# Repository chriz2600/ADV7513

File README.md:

# ADV7513

This is a small development board for the [Analog Devices ADV7513 HDMI Transmitter][ADV7513]. It's designed to be hand-soldered.
I also wrote some code for initialisation (via I2C) in verilog. This can be found as part of my [Dreamcast HDMI][DreamcastHDMI] project. 

[![board][oshpark]][oshparkorder]

[ADV7513]: http://www.analog.com/en/products/audio-video/analoghdmidvi-interfaces/analog-hdmidvi-display-interfaces/adv7513.html
[DreamcastHDMI]: https://github.com/chriz2600/DreamcastHDMI/tree/master/FPGA-CycloneIV-ADV7513

[oshparkorder]: https://oshpark.com/shared_projects/b1enkRm7
[oshpark]: https://oshpark.com/assets/badge-5b7ec47045b78aef6eb9d83b3bac6b1920de805e9a0c227658eac6e19a045b9c.png

### BOM

- `U1`: [ADV7513](http://www.analog.com/en/products/audio-video/analoghdmidvi-interfaces/analog-hdmidvi-display-interfaces/adv7513.html)

    This seems to be a little harder to get from an official distributor, if you are not an HDMI licensee. 
    
    You can get it from [Aliexpress](https://www.aliexpress.com/wholesale?SearchText=ADV7513)

- `U2`: [NCP1117DT33G](https://www.digikey.com/products/en?keywords=NCP1117DT33G)
- `U3`: [NCP1117DT18G](https://www.digikey.com/products/en?keywords=NCP1117DT18G)
- `J1`: [HDMI Connector](https://www.digikey.com/product-detail/en/amphenol-icc-fci/10029449-111RLF/609-4614-1-ND/2785376)
- `U4, U5, U6`: [TVS_DIODE](https://www.digikey.com/product-detail/en/diodes-incorporated/D5V0F4U10MR-13/D5V0F4U10MR-13DICT-ND/4473969)
- `C1, C7, C9, C11, C17, C18`: 10u (0805)
- `C2, C3, C4, C5, C6, C8, C10, C12, C13, C14, C15, C16`: 100n (0805)
- `R1, R2, R5, R6, R7, R8`: 2K (0805)
- `R3`: 887R (0805)
- `R4`: 10K (0805)
- `L1, L2, L3, L4`: 10u (1210)

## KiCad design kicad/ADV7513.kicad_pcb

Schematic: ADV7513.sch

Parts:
C1, C7, C9, C11, C17, C18: 10u; C_0805_HandSoldering
C2, C3, C4, C5, C6, C8, C10, C12, C13, C14, C15, C16: 100n; C_0805_HandSoldering
J1: HDMI; hdmi_new
L1, L2, L3, L4: 10u; R_1210_HandSoldering
P1: 5V; Pin_Header_Straight_1x02_Pitch2.54mm
P2: SYNC; Pin_Header_Straight_2x04_Pitch2.54mm
P3: I2C_INT; Pin_Header_Straight_1x04_Pitch2.54mm
P4: AUDIO; Pin_Header_Straight_2x08_Pitch2.54mm
P5: RED; Pin_Header_Straight_2x08_Pitch2.54mm
P6: GREEN; Pin_Header_Straight_2x08_Pitch2.54mm
P7: BLUE; Pin_Header_Straight_2x08_Pitch2.54mm
R1, R2, R5, R6, R7, R8: 2K; R_0805_HandSoldering
R3: 887R; R_0805_HandSoldering
R4: 10K; R_0805_HandSoldering
U1: ADV7513; HTQFP-64_1EP_10x10mm_Pitch0.5mm_ThermalPad3
U2: NCP1117DT33G; TO-252-2Lead
U3: NCP1117DT18G; TO-252-2Lead
U4, U5, U6: TVS_DIODE_3.3VWM_10VC_SMD; MSOP-10_3x3mm_Pitch0.5mm

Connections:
1V8: C2.1, C3.1, C4.1, C5.1, C18.1, L4.1, U1.1 (DVDD), U1.11 (DVDD), U1.31 (DVDD), U1.51 (DVDD)
3V3: C6.1, C17.1, L3.1, R5.1, R6.1, R7.1, U1.29 (DVDD_3V)
5V: C7.1, C8.1, J1.18, P1.2, R1.1, R2.1, U2.3, U6.4 (Ch2), U6.7 (NC)
AVDD_1V8: C11.1, C12.1, C13.1, C14.1, L2.1, U1.15 (AVDD), U1.19 (AVDD), U1.25 (AVDD)
DDCSCL: J1.15, R1.2, U1.33 (DDCSCL), U6.1 (Ch1), U6.10 (NC)
DDCSDA: J1.16, R2.2, U1.34 (DDCSDA), U6.2 (NC), U6.9 (Ch4)
GND: C1.2, C2.2, C3.2, C4.2, C5.2, C6.2, C7.2, C8.2, C9.2, C10.2, C11.2, C12.2, C13.2, C14.2, C15.2, C16.2, C17.2, C18.2, J1.0, J1.2, J1.5, J1.8, J1.11, J1.13, J1.14, J1.17, P1.1, P2.1, P2.3, P2.5, P2.7, P3.1, P4.1, P4.3, P4.5, P4.7, P4.9, P4.11, P4.13, P4.15, P5.1, P5.3, P5.5, P5.7, P5.9, P5.11, P5.13, P5.15, P6.1, P6.3, P6.5, P6.7, P6.9, P6.11, P6.13, P6.15, P7.1, P7.3, P7.5, P7.7, P7.9, P7.11, P7.13, P7.15, R3.2, R4.2, R8.2, U1.30 (CEC), U1.32 (CEC_CLK), U1.65 (PAD/GND), U2.1, U3.1, U4.8 (GND), U5.8 (GND), U6.8 (GND)
HPD: J1.19, R4.1, U1.16 (HPD), U6.5 (NC), U6.6 (Ch3)
unnamed: C9.1, C10.1, L3.2, U2.2, U3.3
unnamed: L1.2, L2.2, L4.2, U3.2
unnamed: P2.2, U1.63 (DE)
unnamed: P2.4, U1.64 (HSYNC)
unnamed: P2.6, U1.53 (CLK)
unnamed: P2.8, U1.2 (VSYNC)
unnamed: P3.2, R7.2, U1.28 (INT)
unnamed: P3.3, R6.2, U1.35 (SCL)
unnamed: P3.4, R5.2, U1.36 (SDA)
unnamed: P4.2, U1.3 (SPDIF)
unnamed: P4.4, U1.4 (MCLK)
unnamed: P4.6, U1.5 (I2S0)
unnamed: P4.8, U1.6 (I2S1)
unnamed: P4.10, U1.7 (I2S2)
unnamed: P4.12, U1.8 (I2S3)
unnamed: P4.14, U1.9 (SCLK)
unnamed: P4.16, U1.10 (LRCLK)
unnamed: P5.2, U1.37 (DATA23)
unnamed: P5.4, U1.38 (DATA22)
unnamed: P5.6, U1.39 (DATA21)
unnamed: P5.8, U1.40 (DATA20)
unnamed: P5.10, U1.41 (DATA19)
unnamed: P5.12, U1.42 (DATA18)
unnamed: P5.14, U1.43 (DATA17)
unnamed: P5.16, U1.44 (DATA16)
unnamed: P6.2, U1.45 (DATA15)
unnamed: P6.4, U1.46 (DATA14)
unnamed: P6.6, U1.47 (DATA13)
unnamed: P6.8, U1.48 (DATA12)
unnamed: P6.10, U1.49 (DATA11)
unnamed: P6.12, U1.50 (DATA10)
unnamed: P6.14, U1.52 (DATA9)
unnamed: P6.16, U1.54 (DATA8)
unnamed: P7.2, U1.55 (DATA7)
unnamed: P7.4, U1.56 (DATA6)
unnamed: P7.6, U1.57 (DATA5)
unnamed: P7.8, U1.58 (DATA4)
unnamed: P7.10, U1.59 (DATA3)
unnamed: P7.12, U1.60 (DATA2)
unnamed: P7.14, U1.61 (DATA1)
unnamed: P7.16, U1.62 (DATA0)
unnamed: R3.1, U1.14 (R_EXT)
unnamed: R8.1, U1.22 (PD)
PVDD_1V8: C1.1, C15.1, C16.1, L1.1, U1.12 (PVDD), U1.13 (BGVDD)
TX0+: J1.7, U1.21 (TX0+), U4.5 (NC), U4.6 (Ch3)
TX0-: J1.9, U1.20 (TX0-), U4.4 (Ch2), U4.7 (NC)
TX1+: J1.4, U1.24 (TX1+), U5.2 (NC), U5.9 (Ch4)
TX1-: J1.6, U1.23 (TX1-), U5.1 (Ch1), U5.10 (NC)
TX2+: J1.1, U1.27 (TX2+), U5.5 (NC), U5.6 (Ch3)
TX2-: J1.3, U1.26 (TX2-), U5.4 (Ch2), U5.7 (NC)
TXC+: J1.10, U1.18 (TXC+), U4.2 (NC), U4.9 (Ch4)
TXC-: J1.12, U1.17 (TXC-), U4.1 (Ch1), U4.10 (NC)

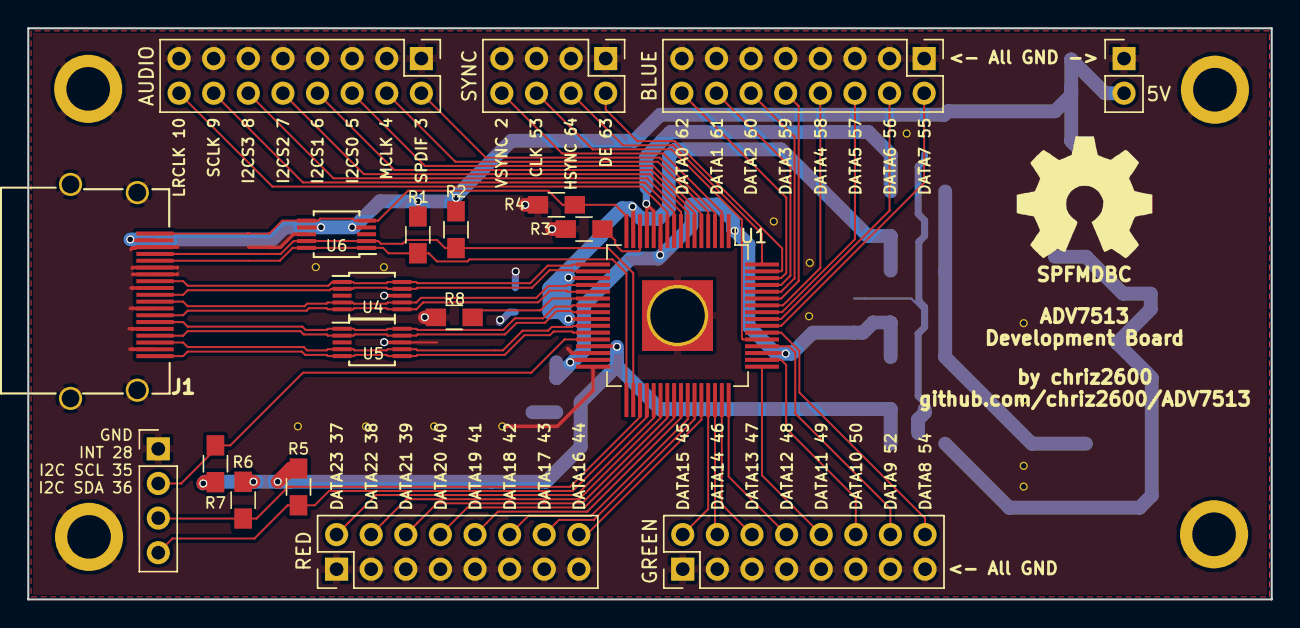
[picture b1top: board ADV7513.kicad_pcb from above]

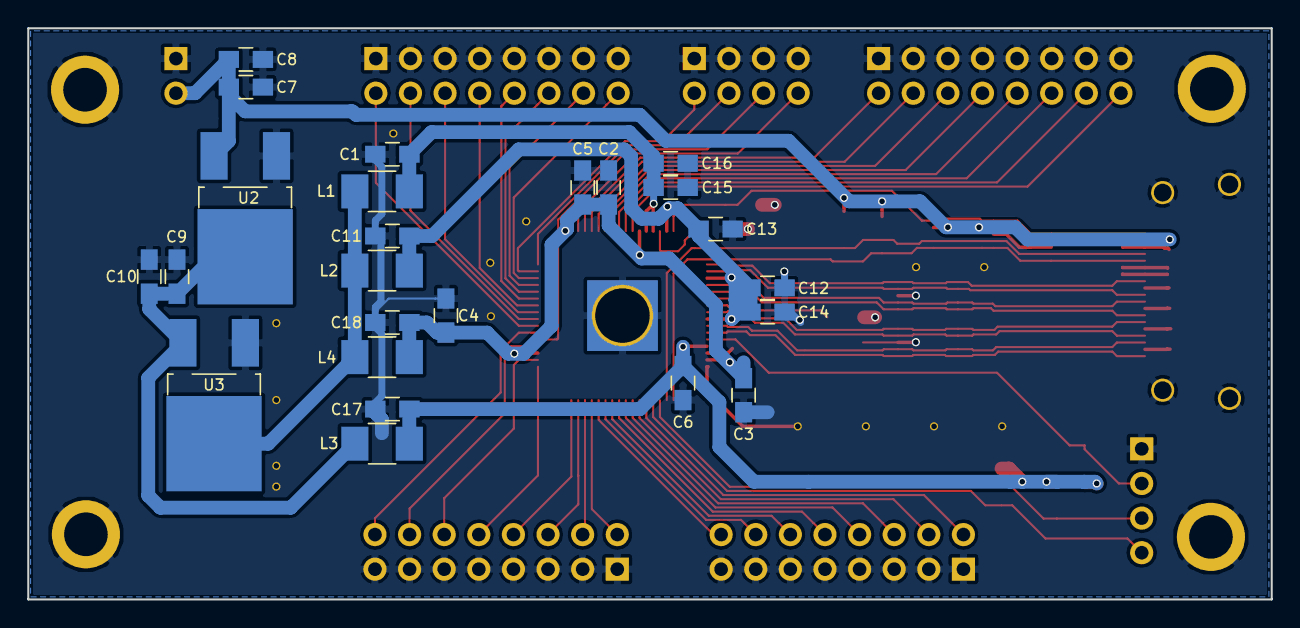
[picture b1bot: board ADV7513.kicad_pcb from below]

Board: 4 copper layers, 91.2 x 41.9 mm, 45 parts (24 on the bottom side), 60 nets.

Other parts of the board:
VAL: REF; OSHW-logo_10mm

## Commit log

2017-03-27 Initial import
2017-03-27 readme updated
2017-03-27 Ground HDMI connector shield
2017-03-27 added oshpark link
2017-03-27 Create LICENSE
2018-03-23 cleaned up libraries
2019-02-16 added bom
